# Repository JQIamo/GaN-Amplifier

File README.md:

# GaN-Amplifier
High-power, wideband RF amplifier designed by D. Barker and A. Restelli.
This design is released under the CERN Open Hardware License v1.2.

Primary documentation for the GaN amplifier can be found in the [Wiki](https://github.com/JQIamo/aom-driver/wiki/AOM-Driver-Wiki) for the [GaN-Amp-Compatible](https://github.com/JQIamo/aom-driver/tree/GaN-Amp-Compatible) branch of the AOM driver.

The eagle files in this repository will be much easier to use with [eagle-config](https://github.com/JQIamo/eagle-config) installed and configured.

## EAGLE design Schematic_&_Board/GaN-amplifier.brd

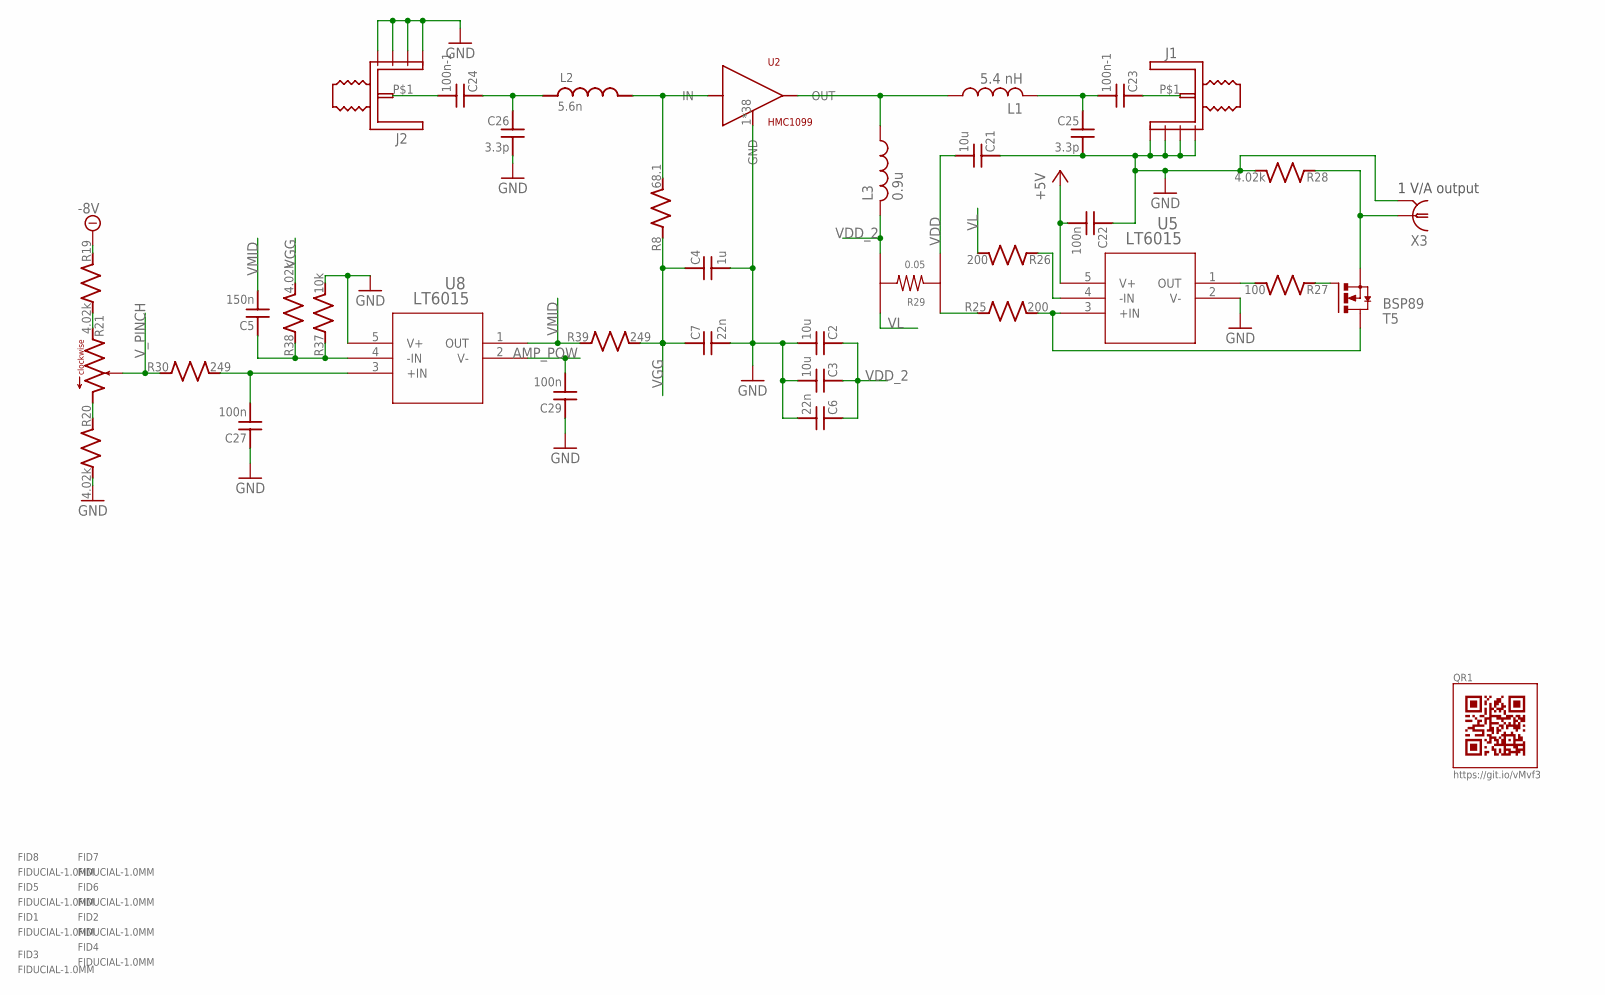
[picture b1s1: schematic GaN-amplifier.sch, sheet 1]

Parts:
C2, C3, C21: 10u; C_MLCC_1210; PARTNO CL32B106KBJNNNE
C4: 1u; C_MLCC_0603; PARTNO CL10B105KA8NNNC
C5: 150n; C_MLCC_0603; PARTNO CL10B154KO8NNNC
C6, C7: 22n; C_MLCC_0603; PARTNO CL10B223KB8NNNC
C22, C27, C29: 100n; C_MLCC_0603; PARTNO CL10B104KB8SFNC
C23, C24: 100n-1; C_MLCC_0402; PARTNO 0402BB104KW500
C25, C26: 3.3p; C_MLCC_0603; PARTNO 600S3R3CT250XT
FID1, FID2, FID3, FID4, FID5, FID6, FID7, FID8: FIDUCIAL-1.0MM; FID_1.0MM
J1, J2: JOHNSON_SMA_EDGE_LAUNCH_142-0701-851; PARTNO 142-0701-851
L1: 5.4 nH; 0906; PARTNO 0906-5JLB
L2: 5.6n; R_0402; PARTNO 0402CS-5N6XJLU
L3: 0.9u; 1008; PARTNO 1008AF-901XKLC
QR1: QR-HTTPS://GIT.IO/VMVF3-LIGHT-SILK
R8: 68.1; R_0603; PARTNO ERJ-3EKF68R1V
R19, R20, R28, R38: 4.02k; R_0603; PARTNO TNPW06034K02BEEA
R21: R_TRIM; RJ24; PARTNO Y006910K0000J9L
R25, R26: 200; R_0603; PARTNO TNPW0603200RBEEA
R27: 100; R_0603; PARTNO ERJ-3EKF1000V
R29: 0.05; 1206_KELVIN; PARTNO LVK12R050DER
R30, R39: 249; R_0603; PARTNO TNPW0603249RBEEA
R37: 10k; R_0603; PARTNO TNPW060310K0BEEA
T5: BSP89; PG-SOT-223; PARTNO BSP89H6327XTSA1
U2: HMC1099; HCP-32-2; PARTNO HMC1099LP5DE
U5, U8: LT6015; TSOT-23_S5; PARTNO LT6015HS5#TRMPBF
X3: BNC-V; PARTNO 5227222-3

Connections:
+5V: C22.P$2 (2), U5.5 (V+); also elsewhere on the board
-8V: R19.P$1 (1); also elsewhere on the board
AMP_POW: C29.P$2 (2), U8.2 (V-); also elsewhere on the board
GND: C2.P$2 (2), C3.P$2 (2), C4.P$2 (2), C6.P$2 (2), C7.P$2 (2), C21.P$1 (1), C22.P$1 (1), C25.P$2 (2), C26.P$2 (2), C27.P$1 (1), C29.P$1 (1), J1.P$2 (GND1), J1.P$3 (GND), J1.P$4 (GND2), J1.P$5 (GND3), J2.P$2 (GND1), J2.P$3 (GND), J2.P$4 (GND2), J2.P$5 (GND3), R20.P$2 (2), R28.P$2 (2), R37.P$2 (2), U2.1 (GND), U2.2 (GND), U2.3 (GND), U2.6 (GND), U2.7 (GND), U2.8 (GND), U2.9 (GND), U2.10 (GND), U2.11 (GND), U2.12 (GND), U2.13 (GND), U2.14 (GND), U2.15 (GND), U2.16 (GND), U2.17 (GND), U2.18 (GND), U2.19 (GND), U2.22 (GND), U2.23 (GND), U2.24 (GND), U2.25 (GND), U2.26 (GND), U2.27 (GND), U2.28 (GND), U2.29 (GND), U2.30 (GND), U2.31 (GND), U2.32 (GND), U2.33 (GND), U2.34 (GND), U2.35 (GND), U2.36 (GND), U2.37 (GND), U2.38 (GND), U2.39 (GND), U2.40 (GND), U2.41 (GND), U2.42 (GND), U5.2 (V-), U8.5 (V+), X3.2; also elsewhere on the board
unnamed: R19.P$2 (2), R21.1
unnamed: R20.P$1 (1), R21.3
unnamed: R25.P$2 (2), T5.2 (D), T5.4 (D), U5.3 (+IN)
unnamed: R27.P$2 (2), U5.1 (OUT)
unnamed: R27.P$1 (1), T5.1 (G)
unnamed: R25.P$1 (1), R29.P$1
unnamed: R28.P$1 (1), T5.3 (S), X3.1
unnamed: R26.P$1 (1), U5.4 (-IN)
unnamed: C23.P$1 (1), J1.P$1
unnamed: C24.P$2 (2), J2.P$1
unnamed: C5.P$1 (1), R37.P$1 (1), R38.P$1 (1), U8.4 (-IN)
unnamed: C23.P$2 (2), C25.P$1 (1), L1.P$2 (2)
unnamed: L1.P$1 (1), L3.P$1 (1), U2.20 (OUT), U2.21 (OUT)
unnamed: C24.P$1 (1), C26.P$1 (1), L2.P$1 (1)
unnamed: C27.P$2 (2), R30.P$2 (2), U8.3 (+IN)
VDD: C21.P$2 (2), R29.P$3; also elsewhere on the board
VDD_2: C2.P$1 (1), C3.P$1 (1), C6.P$1 (1), L3.P$2 (2), R29.P$4
VGG: C4.P$1 (1), C7.P$1 (1), R8.P$1 (1), R38.P$2 (2), R39.P$2 (2)
VL: R26.P$2 (2), R29.P$2
VMID: C5.P$2 (2), R39.P$1 (1), U8.1 (OUT)
V_GATE: L2.P$2 (2), R8.P$2 (2), U2.4 (IN), U2.5 (IN)
V_PINCH: R21.2, R30.P$1 (1); also elsewhere on the board

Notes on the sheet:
1 V/A output

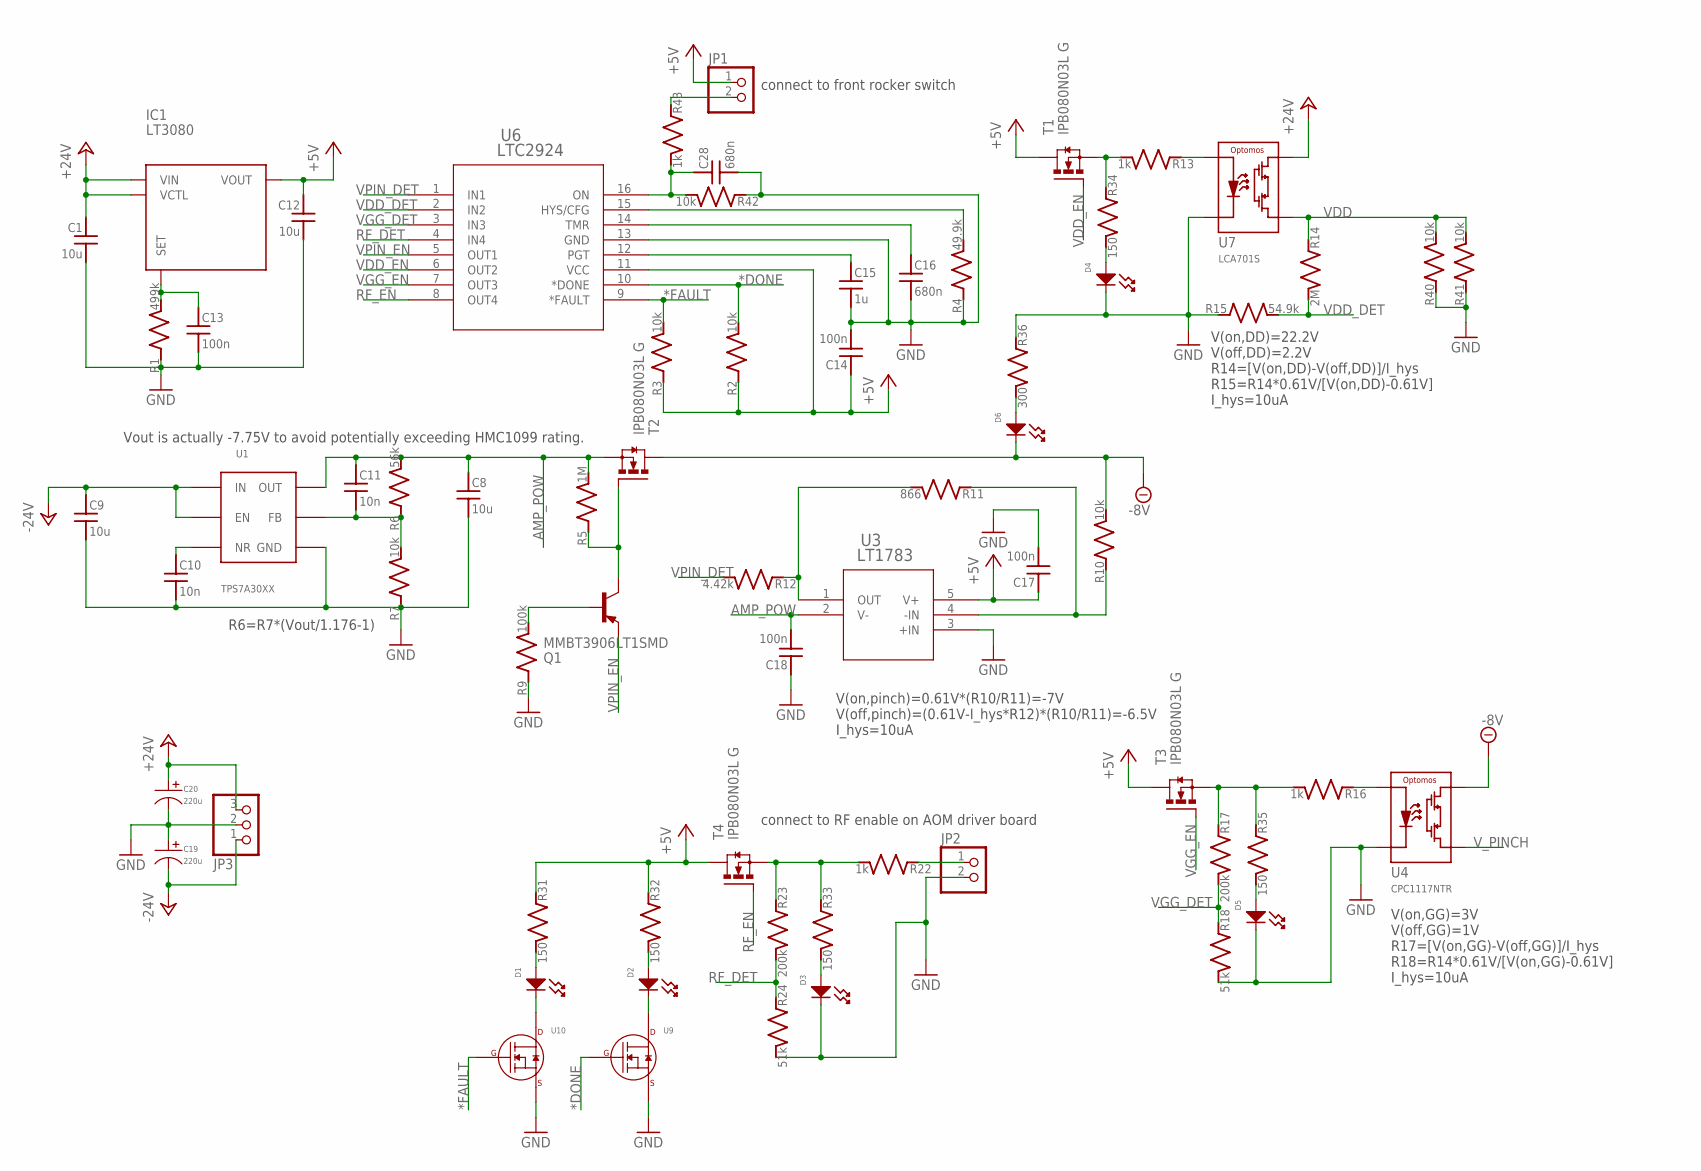
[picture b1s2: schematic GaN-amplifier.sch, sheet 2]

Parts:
C1, C8, C9, C12: 10u; C_MLCC_1210; PARTNO CL32B106KBJNNNE
C10, C11: 10n; C_MLCC_0402; PARTNO CL05B103KB5NNNC
C13, C14, C17, C18: 100n; C_MLCC_0603; PARTNO CL10B104KB8SFNC
C15: 1u; C_MLCC_0603; PARTNO CL10B105KA8NNNC
C16, C28: 680n; C_MLCC_0603; PARTNO CL10B684KO8NFNC
C19, C20: 220u; CP10MM; PARTNO MF-CAP-10MM-220uF
D1, D3, D4, D5, D6: LED_SINGLE-0603-GREEN; LED0603
D2: LED_SINGLE-0603-RED; LED0603
IC1: LT3080; TO263-5; PARTNO LT3080EQ#PBF
JP1, JP2: PINHD-1X2; 1X02; PARTNO 640456-2
JP3: PINHD-1X3; 1X03; PARTNO 640456-3
Q1: MMBT3906LT1SMD; SOT23-BEC; PARTNO MF-DSC-SOT233-MMBT3906
R1: 499k; R_0603; PARTNO ERJ-3EKF4993V
R2, R3, R10, R40, R41, R42: 10k; R_0603; PARTNO ERJ-3EKF1002V
R4: 49.9k; R_0603; PARTNO ERJ-3EKF4992V
R5: 1M; R_0603; PARTNO ERJ-3EKF1004V
R6: 56k; R_0402; PARTNO ERJ-2RKF5602X
R7: 10k; R_0402; PARTNO ERJ-2RKF1002X
R9: 100k; R_0603; PARTNO ERJ-3EKF1003V
R11: 866; R_0603; PARTNO ERJ-3EKF8660V
R12: 4.42k; R_0603; PARTNO ERJ-3EKF4421V
R13, R16, R22, R43: 1k; R_0603; PARTNO ERJ-3EKF1001V
R14: 2M; R_0603; PARTNO ERJ-3EKF2004V
R15: 54.9k; R_0603; PARTNO ERJ-3EKF5492V
R17, R23: 200k; R_0603; PARTNO ERJ-3EKF2003V
R18, R24: 51k; R_0603; PARTNO ERJ-3EKF5102V
R31, R32, R33, R34, R35: 150; R_0603; PARTNO ERJ-3EKF1500V
R36: 300; R_0603; PARTNO ERJ-PA3F3000V
T1, T2, T3, T4: IPB080N03L G; D2PACK; PARTNO IPB080N03L G
U1: TPS7A30XX; DGN; PARTNO TPS7A3001DGNR
U3: LT1783; TSOT-23_S5; PARTNO LT1783HS5#TRMPBF
U4: CPC1117NTR; 4-LEAD_SOP; PARTNO CPC1117NTR
U6: LTC2924; SSOP-16_GN; PARTNO LTC2924IGN#PBF
U7: LCA701S; 6-LEAD_SMT; PARTNO LCA701S
U9, U10: N-CHANNEL_FET_BSS138_SOT-23-3; SOT-23-3

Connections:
*DONE: R2.P$2 (2), U6.10 (*DONE), U9.P$1 (GATE)
*FAULT: R3.P$2 (2), U6.9 (*FAULT), U10.P$1 (GATE)
+5V: C12.P$1 (1), C14.P$1 (1), C17.P$1 (1), IC1.3 (VOUT), IC1.6 (VOUT), JP1.1, R2.P$1 (1), R3.P$1 (1), R31.P$1 (1), R32.P$1 (1), T1.2 (D), T3.2 (D), T4.2 (D), U3.5 (V+), U6.11 (VCC); also elsewhere on the board
+24V: C1.P$1 (1), C20.P$1, IC1.4 (VCTL), IC1.5 (VIN), JP3.3, U7.6 (L+)
-8V: D6.CATHODE, R10.P$2 (2), T2.2 (D), U4.P$4 (L+); also elsewhere on the board
-24V: C9.P$1 (1), C19.P$2, JP3.1, U1.EN, U1.IN
AMP_POW: C8.P$1 (1), C11.P$1 (1), C18.P$2 (2), R5.P$2 (2), R6.P$2 (2), T2.3 (S), U1.OUT, U3.2 (V-); also elsewhere on the board
GND: C1.P$2 (2), C8.P$2 (2), C9.P$2 (2), C10.P$2 (2), C12.P$2 (2), C13.P$2 (2), C14.P$2 (2), C15.P$2 (2), C16.P$2 (2), C17.P$2 (2), C18.P$1 (1), C19.P$1, C20.P$2, C28.P$2 (2), D3.CATHODE, D4.CATHODE, D5.CATHODE, JP2.2, JP3.2, R1.P$1 (1), R4.P$1 (1), R7.P$1 (1), R9.P$1 (1), R15.P$1 (1), R18.P$2 (2), R24.P$2 (2), R36.P$1 (1), R40.P$1 (1), R41.P$1 (1), R42.P$1 (1), U1.GND, U1.GND1 (GND), U3.3 (+IN), U4.P$2 (C-), U6.13 (GND), U7.2 (C-), U9.P$2 (SOURCE), U10.P$2 (SOURCE); also elsewhere on the board
unnamed: C13.P$1 (1), IC1.2 (SET), R1.P$2 (2)
unnamed: D1.CATHODE, U10.P$3 (DRAIN)
unnamed: D2.CATHODE, U9.P$3 (DRAIN)
unnamed: JP1.2, R43.P$1 (1)
unnamed: C16.P$1 (1), U6.14 (TMR)
unnamed: R4.P$2 (2), U6.15 (HYS/CFG)
unnamed: C15.P$1 (1), U6.12 (PGT)
unnamed: R11.P$2 (2), R12.P$1 (1), U3.1 (OUT)
unnamed: Q1.C, R5.P$1 (1), T2.1 (G)
unnamed: Q1.B, R9.P$2 (2)
unnamed: R13.P$2 (2), R34.P$1 (1), T1.3 (S)
unnamed: R10.P$1 (1), R11.P$1 (1), U3.4 (-IN)
unnamed: R13.P$1 (1), U7.1 (C+)
unnamed: R16.P$2 (2), R17.P$1 (1), R35.P$1 (1), T3.3 (S)
unnamed: C11.P$2 (2), R6.P$1 (1), R7.P$2 (2), U1.FB
unnamed: R16.P$1 (1), U4.P$1 (C+)
unnamed: C10.P$1 (1), U1.NR/SS (NR)
unnamed: D1.ANODE, R31.P$2 (2)
unnamed: R22.P$2 (2), R23.P$1 (1), R33.P$1 (1), T4.3 (S)
unnamed: JP2.1, R22.P$1 (1)
unnamed: D2.ANODE, R32.P$2 (2)
unnamed: D4.ANODE, R34.P$2 (2)
unnamed: D3.ANODE, R33.P$2 (2)
unnamed: D5.ANODE, R35.P$2 (2)
unnamed: D6.ANODE, R36.P$2 (2)
unnamed: C28.P$1 (1), R42.P$2 (2), R43.P$2 (2), U6.16 (ON)
RF_DET: R23.P$2 (2), R24.P$1 (1), U6.4 (IN4)
RF_EN: T4.1 (G), U6.8 (OUT4)
VDD: R14.P$1 (1), R40.P$2 (2), R41.P$2 (2), U7.4 (L-); also elsewhere on the board
VDD_DET: R14.P$2 (2), R15.P$2 (2), U6.2 (IN2)
VDD_EN: T1.1 (G), U6.6 (OUT2)
VGG_DET: R17.P$2 (2), R18.P$1 (1), U6.3 (IN3)
VGG_EN: T3.1 (G), U6.7 (OUT3)
VPIN_DET: R12.P$2 (2), U6.1 (IN1)
VPIN_EN: Q1.E, U6.5 (OUT1)
V_PINCH: U4.P$3 (L-); also elsewhere on the board

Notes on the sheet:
Vout is actually -7.75V to avoid potentially exceeding HMC1099 rating.
R6=R7*(Vout/1.176-1)
connect to front rocker switch
V(on,pinch)=0.61V*(R10/R11)=-7V V(off,pinch)=(0.61V-I_hys*R12)*(R10/R11)=-6.5V I_hys=10uA
V(on,DD)=22.2V V(off,DD)=2.2V R14=[V(on,DD)-V(off,DD)]/I_hys R15=R14*0.61V/[V(on,DD)-0.61V] I_hys=10uA
V(on,GG)=3V V(off,GG)=1V R17=[V(on,GG)-V(off,GG)]/I_hys R18=R14*0.61V/[V(on,GG)-0.61V] I_hys=10uA
connect to RF enable on AOM driver board

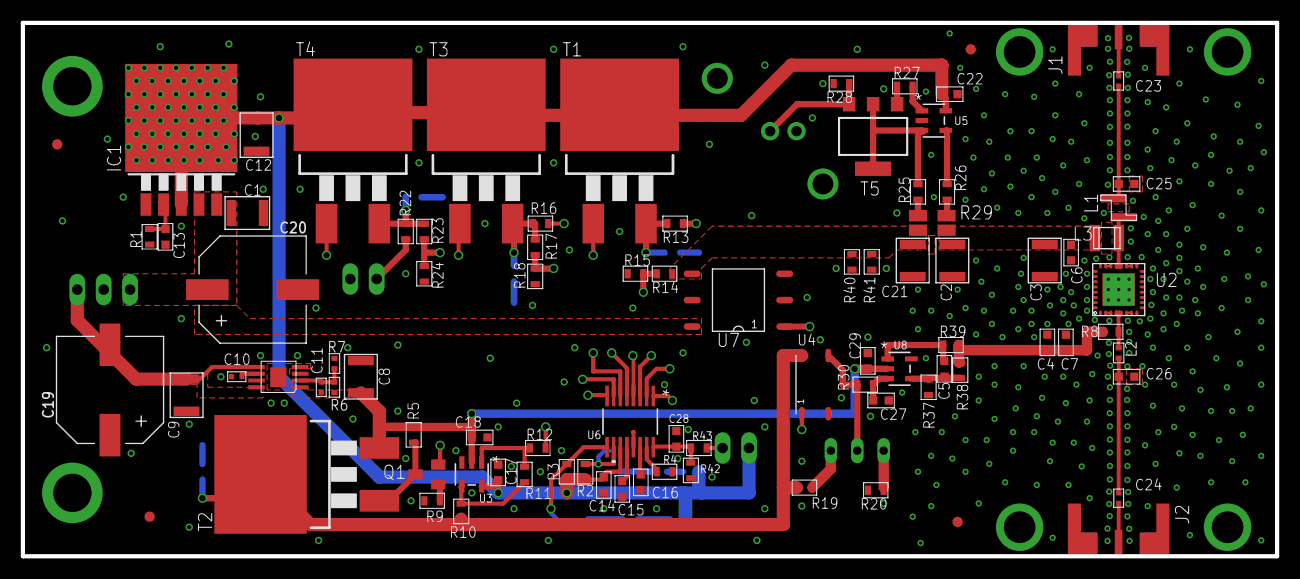
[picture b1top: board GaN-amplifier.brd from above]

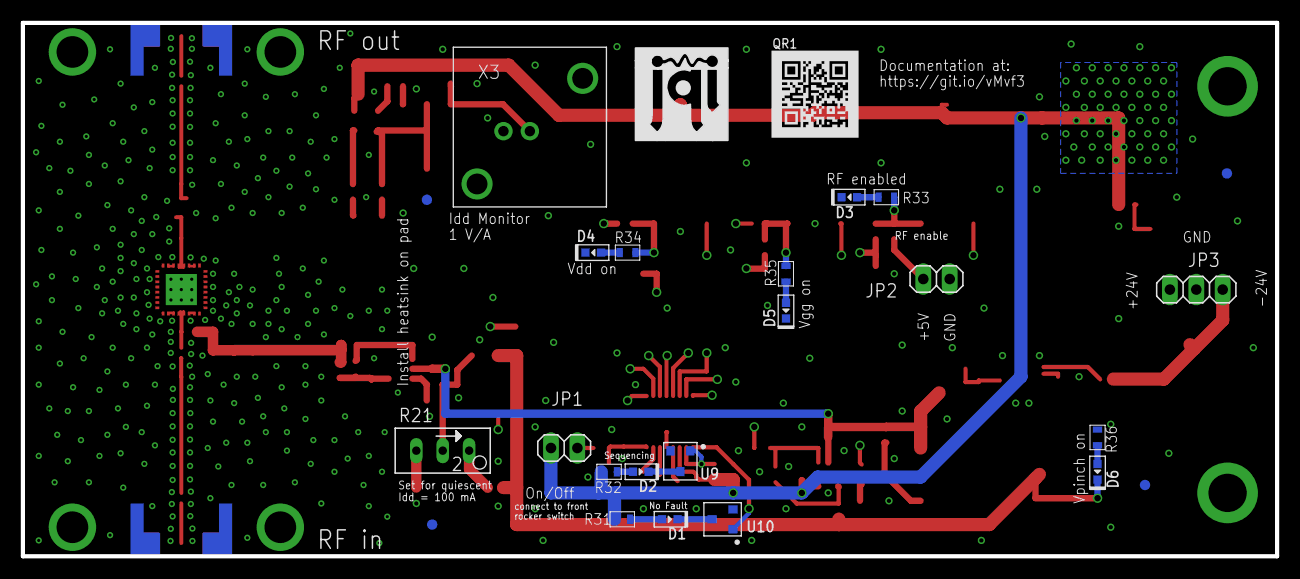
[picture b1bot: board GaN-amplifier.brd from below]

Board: 4 copper layers, 120.7 x 51.3 mm, 114 parts (25 on the bottom side), 64 nets.

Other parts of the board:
U$2: JQI_LOGO_NEGATIVE-SILKSCREEN

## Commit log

2016-11-29 Initial Push
    Started circuit design for the GaN amplifier.
    DSB
2016-11-29 Add .gitignore
2016-11-30 Mostly designed power sequencing
    This will all almost certainly be trashed, but it's a start.
    DSB
2016-12-02 Change power sequencing
    Switched to using LTC2924 for power sequencing.
    DSB
2016-12-05 Halfway done with power sequencing
    The gate voltage supply and bias supply sequencing should be good to
    go. Still need to set up the gate voltage and RF power lockout.
    DSB
2016-12-05 Quick Sync to talk sequencing with AR
    A few more updates to discuss.
    DSB
2016-12-07 Starting Vgg Control
    Started setting up the power sequencing and setpoint control for the
    amplifier gate voltage.
    DSB
2016-12-08 Finished Power Sequencing
    Completed the power sequencing section. Starting on the RF amp section.
    Need to track down the correct inductors.
    DSB
2016-12-09 Mostly done with schematic
    Just need to find that damn bias-t inductor.
    DSB
2016-12-12 Finished Schematic
    Found a bias inductor, so the schematic is finished. I'll want to get
    the board layed out this week so that a test piece can be ordered before
    Xmas.
    DSB
2016-12-12 Started board layout
    Moved all the components so they fit in the allowed area. Need to
    detangle air wires next.
    DSB
2016-12-14 Parts positioned
    I've positioned the components. Now routing needs to happen.
    DSB
2016-12-15 Few adjustments
    Rearranged the board to be a bit more compact.
    DSB
2016-12-16 Power Sequencing Layed Out
    I've finished routing the power sequencing part of the PCB. Need to copy
    positions of RF components from eval board gerber and design 50 Ohm
    striplines.
    DSB
2016-12-19 Add VGG Buffer
    Added buffer for the GaN amp gate voltage. Also made progress on RF
    layout.
    DSB
2016-12-20 Routed Buffer
    I’ve routed the gate bias buffer part of the circuit. The only thing
    that’s left is routing the RF traces.
    DSB
2016-12-20 Finished Layout, Starting BOM
    I've finished the layout up to getting final RF trace widths set (per
    manufacturer specs) and started compiling a BOM.
    DSB
2016-12-21 Finished BOM
    All parts are now added to BOM.
    DSB
2016-12-21 Finalizing Design
    I've almost finalized the design. Just need to order the HMC1099 and
    ensure that Macrofab can do the job properly.
    DSB
2016-12-22 Updated BOM and Mirrored Parts
    Changed BOM for better compatibility with MacroFab. Changed the
    through-hole components to populate on the bottom of the board.
    DSB
2016-12-22 Added Error Monitor LEDs
    Added a couple LEDs to indicate the status of the power sequencer.
    DSB
2016-12-23 QR and more LEDs
    I added a few more indicator LEDs and a QR code that points to the
    repository.
    DSB
2017-01-03 Prepared to order
    Made a few adjustments based on Alessandro's suggestions. Ready to order
    once consigned parts arrive.
    DSB
2017-01-11 Fixes per Alessandro
    Added LP-filter for gate voltage and GND plane cutouts to improve RF
    performance. Also switched a few components for equivalent parts to
    reduce cost.
    DSB
2017-01-11 Tweak silkscreen
    Exactly what it sounds like.
    DSB
2017-01-11 Separate RF and Sequencing
    I've moved the RF and power sequencing portions of the circuit diagram
    to separate sheets for readability.
    DSB
2017-01-12 Moved few vias nearer to the RF microstrip
    Please check that the LTC1152 is not modulating the amplitude of the RF
    carrier at 4 MHz introducing sidebands.
2017-01-12 New Vgg Buffer
    Changed out the Vgg buffer IC to reduce noise.
    DSB
2017-03-04 Fixed U4 package
    Updated board layout with correct optomos package.
    DSB
2017-03-08 Updated MacroFab Files
    Updated Macrofab files with the new optomos package.
    DSB
2017-03-13 Updates per test board
    Adding pulldown on Vdd and On/Off to prevent errors during power
    sequencing. Also increasing capacitance of AC coupling capacitors for
    better low frequency performance. A couple cosmetic changes to make
    component labels visible.
    DSB
2017-04-20 More test board updates
    Adjusted fiducial position per Zach's advice and added switch debouncing
    components.
    DSB
2017-05-09 Changed coupling caps
    I changed the RF coupling capacitors to a lower ESR component. We should
    consider an ultra-broadband cap also, but the expense seems excessive.
    DSB
2017-05-17 Enlarging heatsink pad
    Enlarging the pad for the backside heatsink and adding vias for better
    power dissipation.
    DSB
2017-05-19 Updated BOM and hole positions
    I've changed a couple parts in the BOM and adjusted the position of
    mounting holes to accomodate the new heatsink.
    DSB
2017-06-01 Cosmetic Changes
    Adjusted position of RF in/out labels for visibility with larger
    heatsink.
    DSB
2017-06-14 Adjusted hole sizes
    Changed the mounting hole sizes to increase flexibility.
    DSB
2017-07-06 Better Thermal Management
    Added Vias for better heat dissipation from voltage regulators.
    DSB
2018-02-08 add gitignore
    Adding gitignore to reduce proliferation of tracked eagle files.
    DSB
2018-02-26 Add License
    Added the CERN OHL.
    DSB
2018-02-26 Add License try 2
    Adding the CERN OHL again. Maybe no problems this time.
    DSB

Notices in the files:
parts and their libraries:
COPYRIGHT: Copyright C 2016 Accelerated Designs. All rights reserved
